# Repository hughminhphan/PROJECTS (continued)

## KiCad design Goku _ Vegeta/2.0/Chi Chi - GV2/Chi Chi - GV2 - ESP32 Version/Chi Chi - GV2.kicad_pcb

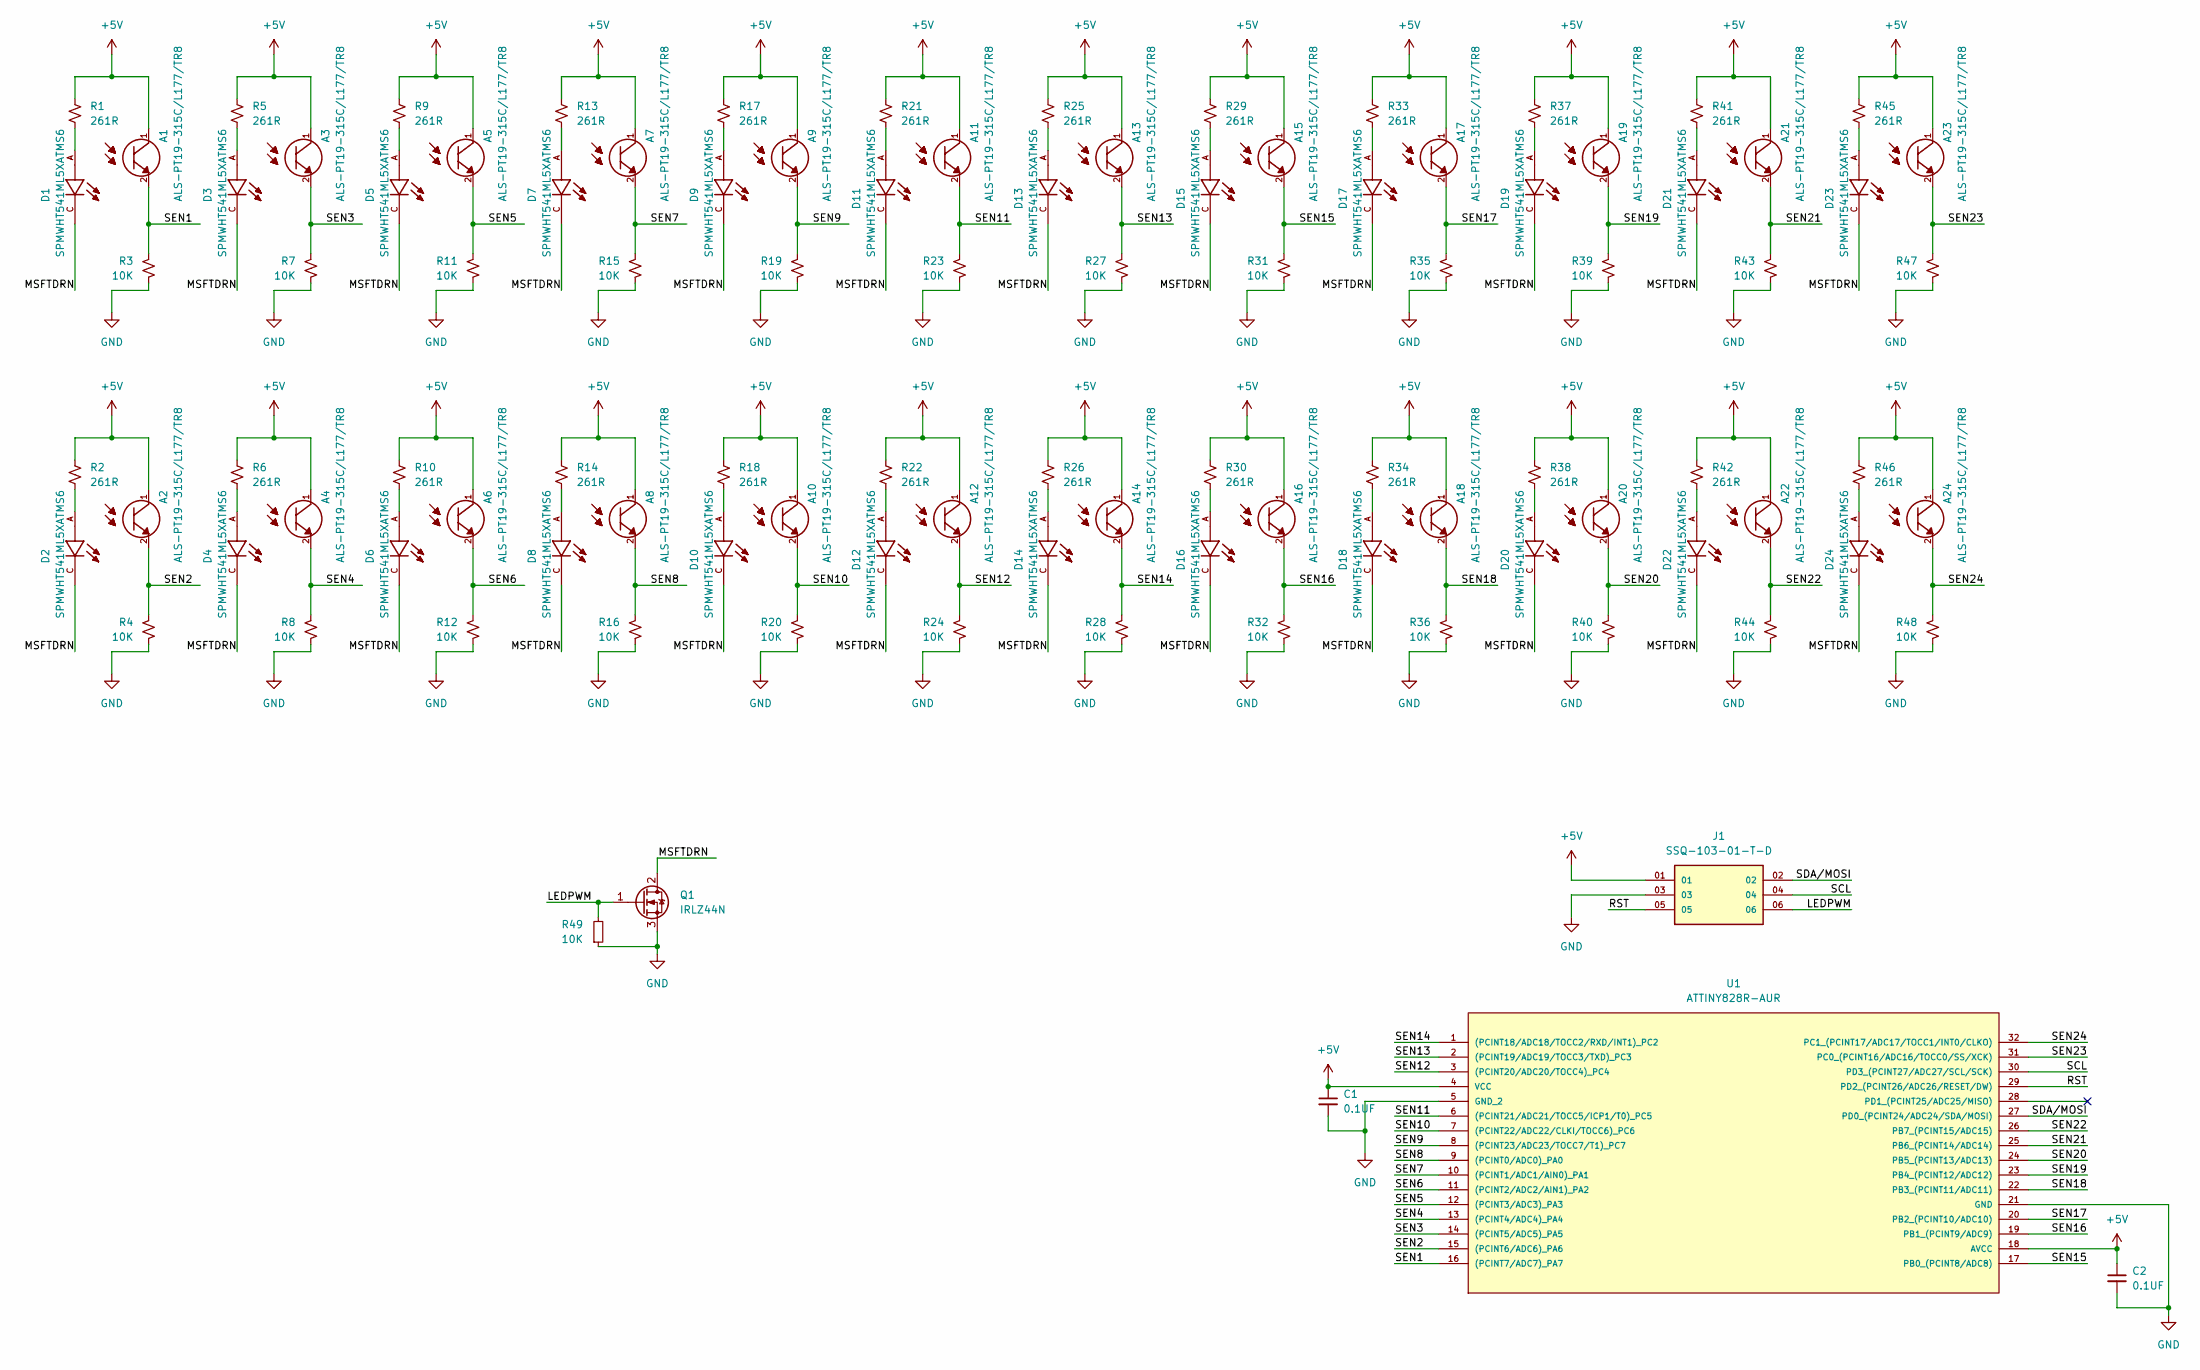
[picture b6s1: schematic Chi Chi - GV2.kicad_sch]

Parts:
A1, A2, A3, A4, A5, A6, A7, A8, A9, A10, A11, A12, A13, A14, A15, A16, A17, A18, A19, A20, A21, A22, A23, A24: ALS-PT19-315C/L177/TR8; XDCR_ALS-PT19-315C_L177_TR8; PARTREV 5
C1, C2: 0.1UF; C_0805_2012Metric_Pad1.18x1.45mm_HandSolder
D1, D2, D3, D4, D5, D6, D7, D8, D9, D10, D11, D12, D13, D14, D15, D16, D17, D18, D19, D20, D21, D22, D23, D24: SPMWHT541ML5XATMS6; LED_SPMWHT541MP5WAPKS4; PARTREV 8.3
J1: SSQ-103-01-T-D; SAMTEC_SSQ-103-01-T-D; PARTREV R
Q1: IRLZ44N; TO-220-3_Vertical
R1, R2, R5, R6, R9, R10, R13, R14, R17, R18, R21, R22, R25, R26, R29, R30, R33, R34, R37, R38, R41, R42, R45, R46: 261R; R_0805_2012Metric_Pad1.20x1.40mm_HandSolder
R3, R4, R7, R8, R11, R12, R15, R16, R19, R20, R23, R24, R27, R28, R31, R32, R35, R36, R39, R40, R43, R44, R47, R48: 10K; R_0805_2012Metric_Pad1.20x1.40mm_HandSolder
R49: 10K; R_0805_2012Metric
U1: ATTINY828R-AUR; TQFP32_9X9_MCH; MANUFACTURER_PART_NUMBER ATTINY828R-AUR

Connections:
+5V: A1.1, A2.1, A3.1, A4.1, A5.1, A6.1, A7.1, A8.1, A9.1, A10.1, A11.1, A12.1, A13.1, A14.1, A15.1, A16.1, A17.1, A18.1, A19.1, A20.1, A21.1, A22.1, A23.1, A24.1, C1.1, C2.1, J1.01, R1.1, R2.1, R5.1, R6.1, R9.1, R10.1, R13.1, R14.1, R17.1, R18.1, R21.1, R22.1, R25.1, R26.1, R29.1, R30.1, R33.1, R34.1, R37.1, R38.1, R41.1, R42.1, R45.1, R46.1, U1.4 (VCC), U1.18 (AVCC)
/LEDPWM: J1.06, Q1.1 (G), R49.2
/MSFTDRN: D1.C, D2.C, D3.C, D4.C, D5.C, D6.C, D7.C, D8.C, D9.C, D10.C, D11.C, D12.C, D13.C, D14.C, D15.C, D16.C, D17.C, D18.C, D19.C, D20.C, D21.C, D22.C, D23.C, D24.C, Q1.2 (D)
/RST: J1.05, U1.29 (PD2_(PCINT26/ADC26/RESET/DW))
/SCL: J1.04, U1.30 (PD3_(PCINT27/ADC27/SCL/SCK))
/SDA/MOSI: J1.02, U1.27 (PD0_(PCINT24/ADC24/SDA/MOSI))
/SEN1: A1.2, R3.2, U1.16 ((PCINT7/ADC7)_PA7)
/SEN2: A2.2, R4.2, U1.15 ((PCINT6/ADC6)_PA6)
/SEN3: A3.2, R7.2, U1.14 ((PCINT5/ADC5)_PA5)
/SEN4: A4.2, R8.2, U1.13 ((PCINT4/ADC4)_PA4)
/SEN5: A5.2, R11.2, U1.12 ((PCINT3/ADC3)_PA3)
/SEN6: A6.2, R12.2, U1.11 ((PCINT2/ADC2/AIN1)_PA2)
/SEN7: A7.2, R15.2, U1.10 ((PCINT1/ADC1/AIN0)_PA1)
/SEN8: A8.2, R16.2, U1.9 ((PCINT0/ADC0)_PA0)
/SEN9: A9.2, R19.2, U1.8 ((PCINT23/ADC23/TOCC7/T1)_PC7)
/SEN10: A10.2, R20.2, U1.7 ((PCINT22/ADC22/CLKI/TOCC6)_PC6)
/SEN11: A11.2, R23.2, U1.6 ((PCINT21/ADC21/TOCC5/ICP1/T0)_PC5)
/SEN12: A12.2, R24.2, U1.3 ((PCINT20/ADC20/TOCC4)_PC4)
/SEN13: A13.2, R27.2, U1.2 ((PCINT19/ADC19/TOCC3/TXD)_PC3)
/SEN14: A14.2, R28.2, U1.1 ((PCINT18/ADC18/TOCC2/RXD/INT1)_PC2)
/SEN15: A15.2, R31.2, U1.17 (PB0_(PCINT8/ADC8))
/SEN16: A16.2, R32.2, U1.19 (PB1_(PCINT9/ADC9))
/SEN17: A17.2, R35.2, U1.20 (PB2_(PCINT10/ADC10))
/SEN18: A18.2, R36.2, U1.22 (PB3_(PCINT11/ADC11))
/SEN19: A19.2, R39.2, U1.23 (PB4_(PCINT12/ADC12))
/SEN20: A20.2, R40.2, U1.24 (PB5_(PCINT13/ADC13))
/SEN21: A21.2, R43.2, U1.25 (PB6_(PCINT14/ADC14))
/SEN22: A22.2, R44.2, U1.26 (PB7_(PCINT15/ADC15))
/SEN23: A23.2, R47.2, U1.31 (PC0_(PCINT16/ADC16/TOCC0/SS/XCK))
/SEN24: A24.2, R48.2, U1.32 (PC1_(PCINT17/ADC17/TOCC1/INT0/CLKO))
GND: C1.2, C2.2, J1.03, Q1.3 (S), R3.1, R4.1, R7.1, R8.1, R11.1, R12.1, R15.1, R16.1, R19.1, R20.1, R23.1, R24.1, R27.1, R28.1, R31.1, R32.1, R35.1, R36.1, R39.1, R40.1, R43.1, R44.1, R47.1, R48.1, R49.1, U1.5 (GND_2), U1.21 (GND)
unnamed: D1.A, R1.2
unnamed: D2.A, R2.2
unnamed: D3.A, R5.2
unnamed: D4.A, R6.2
unnamed: D5.A, R9.2
unnamed: D6.A, R10.2
unnamed: D7.A, R13.2
unnamed: D8.A, R14.2
unnamed: D9.A, R17.2
unnamed: D10.A, R18.2
unnamed: D11.A, R21.2
unnamed: D12.A, R22.2
unnamed: D13.A, R25.2
unnamed: D14.A, R26.2
unnamed: D15.A, R29.2
unnamed: D16.A, R30.2
unnamed: D17.A, R33.2
unnamed: D18.A, R34.2
unnamed: D19.A, R37.2
unnamed: D20.A, R38.2
unnamed: D21.A, R41.2
unnamed: D22.A, R42.2
unnamed: D23.A, R45.2
unnamed: D24.A, R46.2

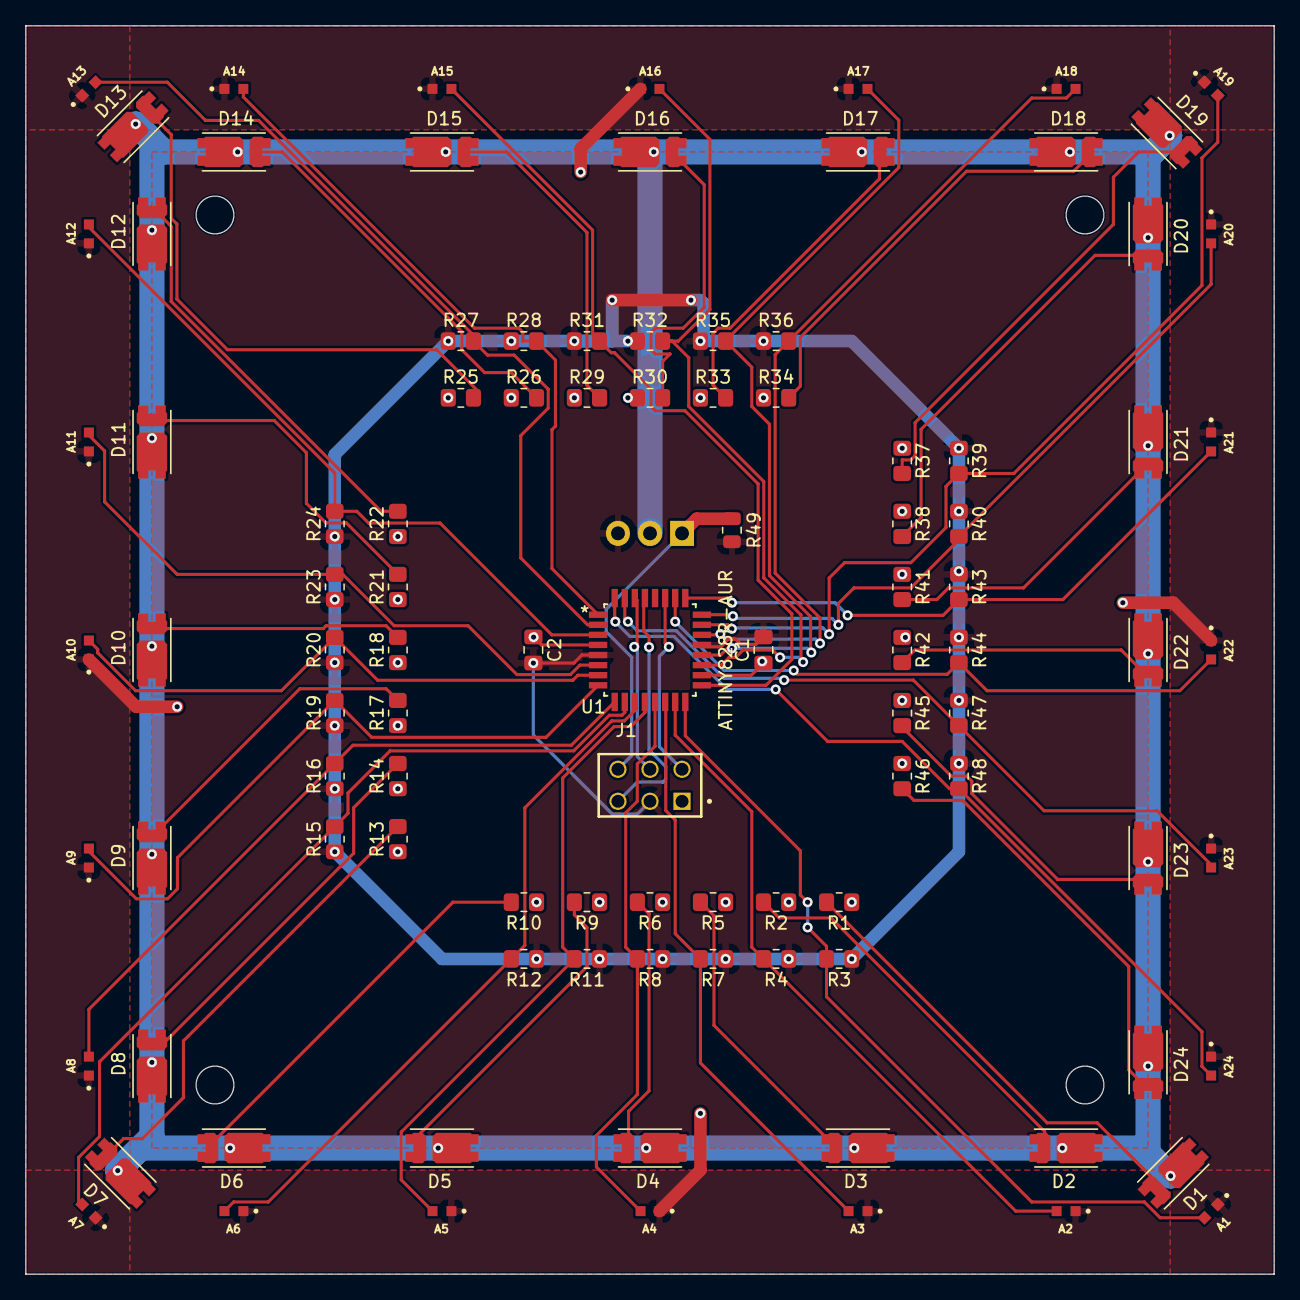
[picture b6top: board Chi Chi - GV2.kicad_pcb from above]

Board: 2 copper layers, 99.0 x 99.0 mm, 102 parts (1 on the bottom side), 55 nets.

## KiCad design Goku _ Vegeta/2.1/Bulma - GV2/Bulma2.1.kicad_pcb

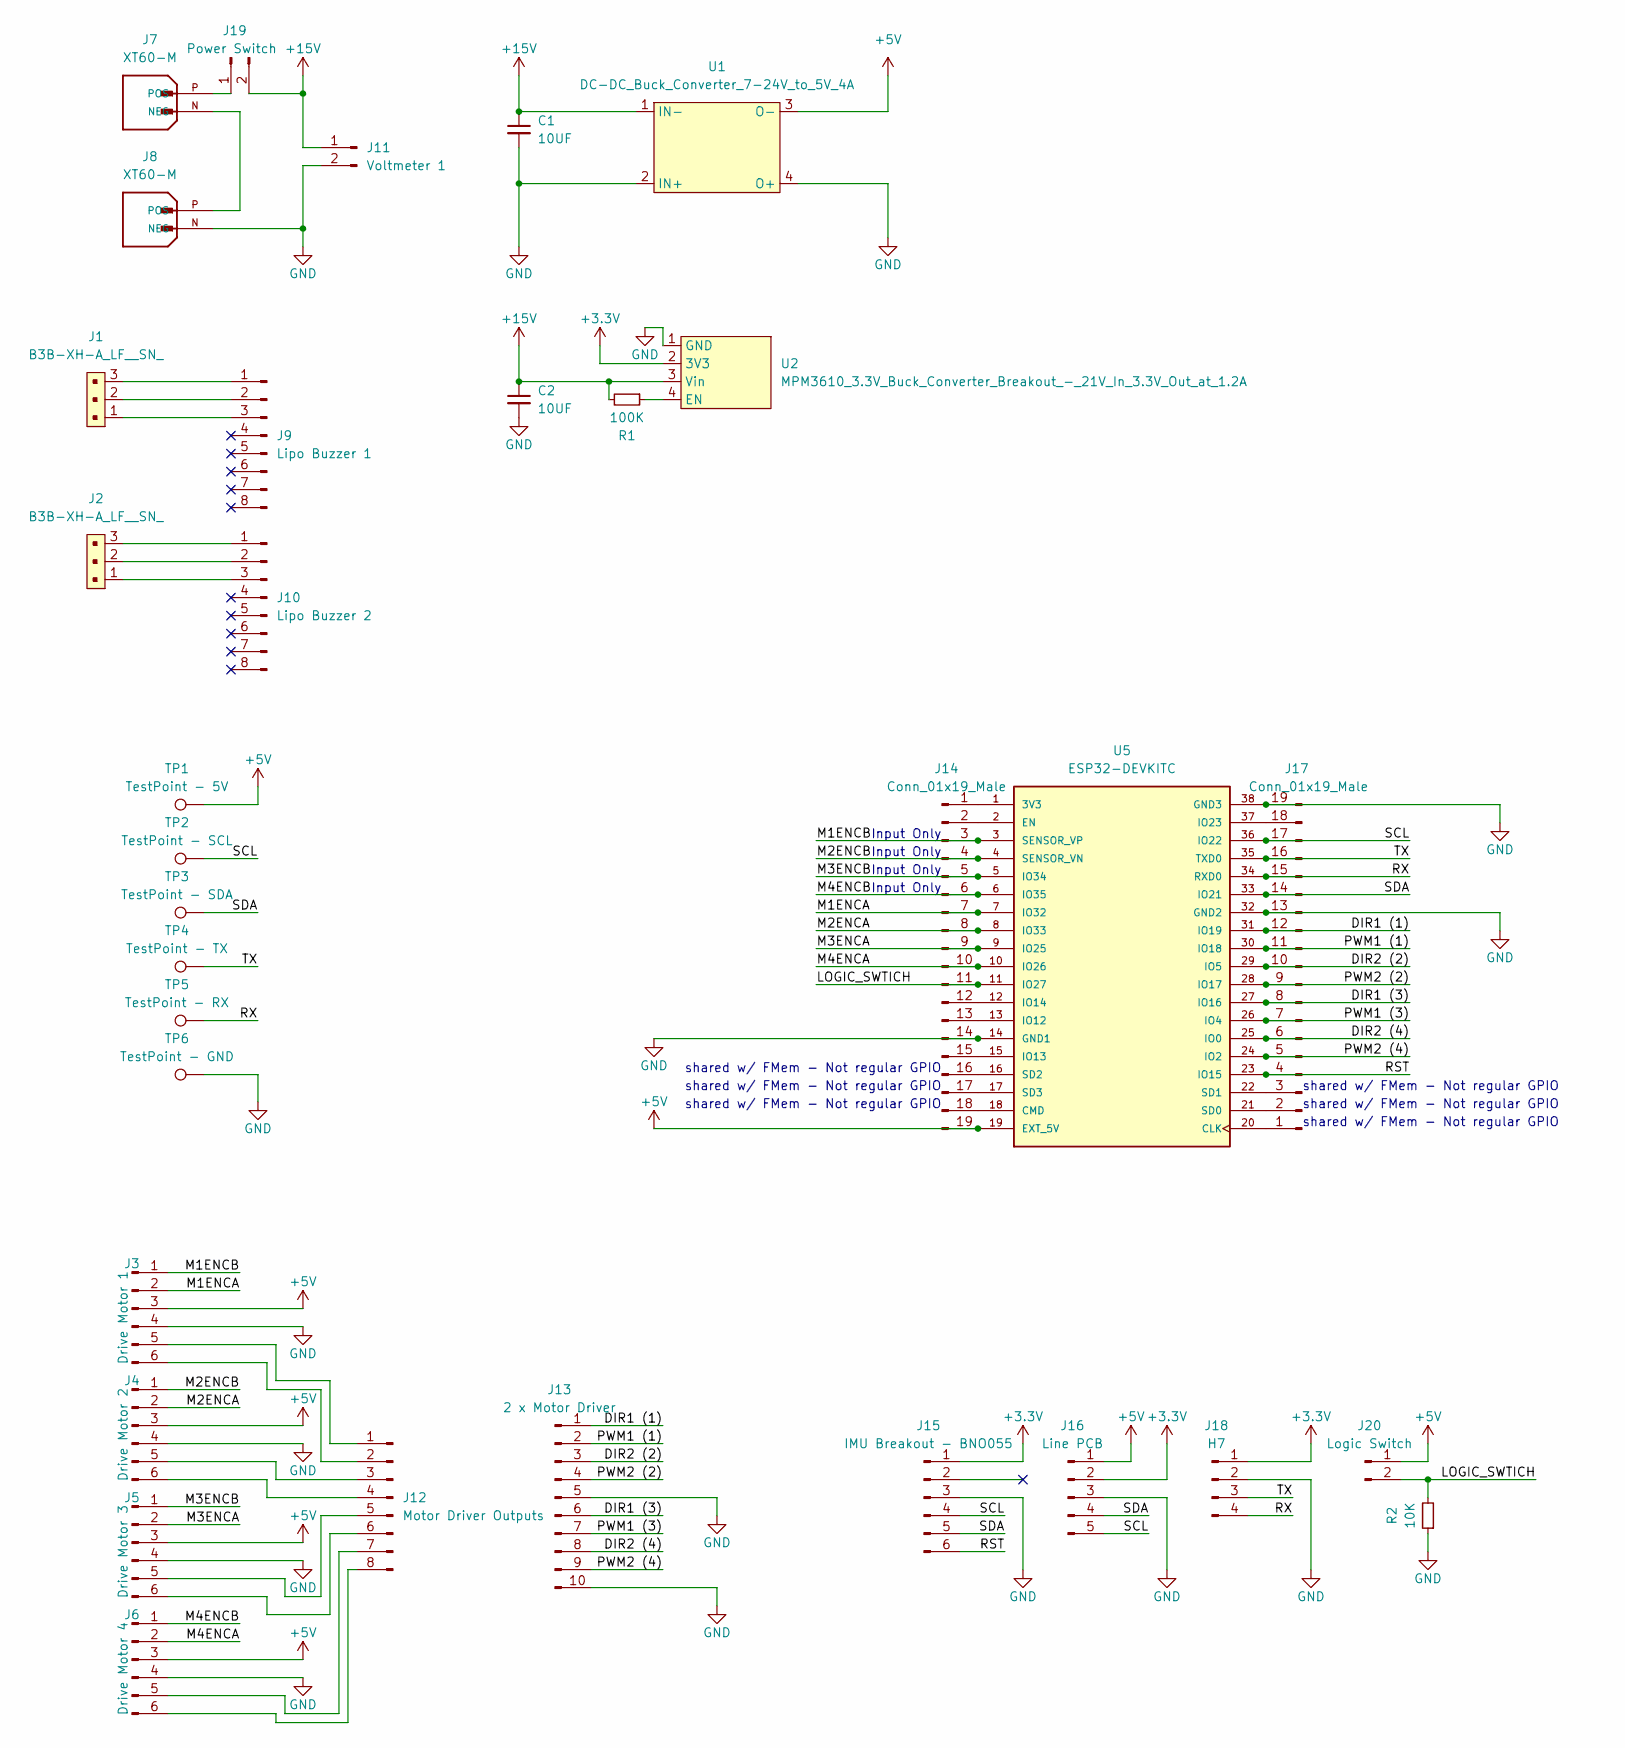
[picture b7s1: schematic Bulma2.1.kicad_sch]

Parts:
C1, C2: 10UF; C_0805_2012Metric
J1, J2: B3B-XH-A_LF__SN_; PinHeader_1x3_P2.5mm_Drill1.1mm; MPN B3B-XH-A(LF)(SN); Digi-Key_PN 455-2248-ND
J3: Drive Motor 1; PinSocket_1x06_P2.54mm_Vertical
J4: Drive Motor 2; PinHeader_1x06_P2.54mm_Vertical
J5: Drive Motor 3; PinSocket_1x06_P2.54mm_Vertical
J6: Drive Motor 4; PinSocket_1x06_P2.54mm_Vertical
J7, J8: XT60-M; AMASS_XT60-M; PARTREV V1.2
J9: Lipo Buzzer 1; Lipo Buzzer Vertical
J10: Lipo Buzzer 2; Lipo Buzzer Vertical
J11: Voltmeter 1; PinHeader_1x02_P2.54mm_Vertical
J12: Motor Driver Outputs; PinHeader_1x08_P2.54mm_Vertical
J13: 2 x Motor Driver; PinHeader_1x10_P2.54mm_Vertical
J14, J17: Conn_01x19_Male; PinHeader_1x19_P2.54mm_Vertical
J15: IMU Breakout - BNO055; Adafruit IMU BNO055
J16: Line PCB; PinHeader_1x05_P2.54mm_Vertical
J18: H7; PinHeader_1x04_P2.54mm_Vertical
J19: Power Switch; PinHeader_1x02_P2.54mm_Vertical
J20: Logic Switch; PinHeader_1x02_P2.54mm_Vertical
R1: 100K; R_0805_2012Metric
R2: 10K; R_0805_2012Metric
TP1: TestPoint - 5V; TestPoint_THTPad_D2.0mm_Drill1.0mm
TP2: TestPoint - SCL; TestPoint_THTPad_D2.0mm_Drill1.0mm
TP3: TestPoint - SDA; TestPoint_THTPad_D2.0mm_Drill1.0mm
TP4: TestPoint - TX; TestPoint_THTPad_D2.0mm_Drill1.0mm
TP5: TestPoint - RX; TestPoint_THTPad_D2.0mm_Drill1.0mm
TP6: TestPoint - GND; TestPoint_THTPad_D2.0mm_Drill1.0mm
U1: DC-DC_Buck_Converter_7-24V_to_5V_4A
U2: MPM3610_3.3V_Buck_Converter_Breakout_-_21V_In_3.3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; MPM3610 3.3V Buck Converter Breakout - 21V In 3.3V Out at 1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
U5: ESP32-DEVKITC; MODULE_ESP32-DEVKITC; PARTREV N/A

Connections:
+3.3V: J15.1, J16.2, J18.1, U2.2 (3V3)
+5V: J3.3, J4.3, J5.3, J6.3, J14.19, J16.1, J20.1, TP1.1, U1.3 (O-), U5.19 (EXT_5V)
+15V: C1.1, C2.1, J11.1, J19.2, R1.2, U1.1 (IN-), U2.3 (Vin)
/DIR1 (1): J13.1, J17.12, U5.31 (IO19)
/DIR1 (3): J13.6, J17.8, U5.27 (IO16)
/DIR2 (2): J13.3, J17.10, U5.29 (IO5)
/DIR2 (4): J13.8, J17.6, U5.25 (IO0)
/LOGIC_SWTICH: J14.11, J20.2, R2.2, U5.11 (IO27)
/M1ENCA: J3.2, J14.7, U5.7 (IO32)
/M1ENCB: J3.1, J14.3, U5.3 (SENSOR_VP)
/M2ENCA: J4.2, J14.8, U5.8 (IO33)
/M2ENCB: J4.1, J14.4, U5.4 (SENSOR_VN)
/M3ENCA: J5.2, J14.9, U5.9 (IO25)
/M3ENCB: J5.1, J14.5, U5.5 (IO34)
/M4ENCA: J6.2, J14.10, U5.10 (IO26)
/M4ENCB: J6.1, J14.6, U5.6 (IO35)
/PWM1 (1): J13.2, J17.11, U5.30 (IO18)
/PWM1 (3): J13.7, J17.7, U5.26 (IO4)
/PWM2 (2): J13.4, J17.9, U5.28 (IO17)
/PWM2 (4): J13.9, J17.5, U5.24 (IO2)
/RST: J15.6, J17.4, U5.23 (IO15)
/RX: J17.15, J18.4, TP5.1, U5.34 (RXD0)
/SCL: J15.4, J16.5, J17.17, TP2.1, U5.36 (IO22)
/SDA: J15.5, J16.4, J17.14, TP3.1, U5.33 (IO21)
/TX: J17.16, J18.3, TP4.1, U5.35 (TXD0)
GND: C1.2, C2.2, J3.4, J4.4, J5.4, J6.4, J8.N (NEG), J11.2, J13.5, J13.10, J14.14, J15.3, J16.3, J17.13, J17.19, J18.2, R2.1, TP6.1, U1.2 (IN+), U1.4 (O+), U2.1 (GND), U5.14 (GND1), U5.32 (GND2), U5.38 (GND3)
unnamed: J7.N (NEG), J8.P (POS)
unnamed: J1.3, J9.1
unnamed: J1.2, J9.2
unnamed: J1.1, J9.3
unnamed: J2.3, J10.1
unnamed: J2.2, J10.2
unnamed: J2.1, J10.3
unnamed: J3.5, J12.1
unnamed: J3.6, J12.2
unnamed: J4.5, J12.3
unnamed: J4.6, J12.4
unnamed: J5.5, J12.5
unnamed: J5.6, J12.6
unnamed: J6.5, J12.7
unnamed: J6.6, J12.8
unnamed: J14.1, U5.1 (3V3)
unnamed: J14.2, U5.2 (EN)
unnamed: J14.12, U5.12 (IO14)
unnamed: J14.13, U5.13 (IO12)
unnamed: J14.15, U5.15 (IO13)
unnamed: J14.16, U5.16 (SD2)
unnamed: J14.17, U5.17 (SD3)
unnamed: J14.18, U5.18 (CMD)
unnamed: J17.1, U5.20 (CLK)
unnamed: J17.2, U5.21 (SD0)
unnamed: J17.3, U5.22 (SD1)
unnamed: J17.18, U5.37 (IO23)
unnamed: J7.P (POS), J19.1
unnamed: R1.1, U2.4 (EN)

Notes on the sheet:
Input Only
shared w/ FMem - Not regular GPIO

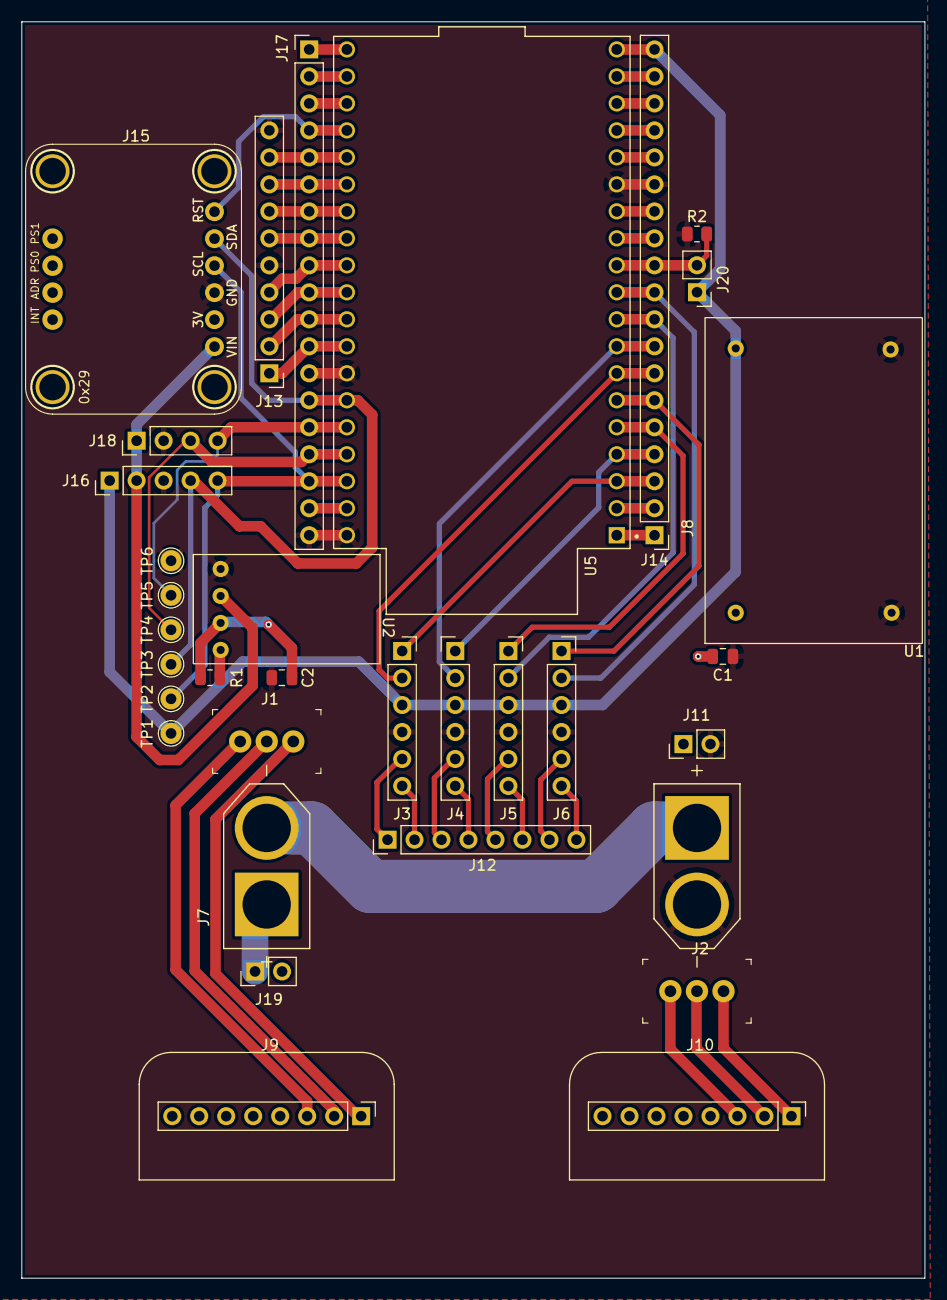
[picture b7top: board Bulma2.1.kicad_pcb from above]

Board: 2 copper layers, 85.0 x 118.2 mm, 33 parts (0 on the bottom side), 55 nets.

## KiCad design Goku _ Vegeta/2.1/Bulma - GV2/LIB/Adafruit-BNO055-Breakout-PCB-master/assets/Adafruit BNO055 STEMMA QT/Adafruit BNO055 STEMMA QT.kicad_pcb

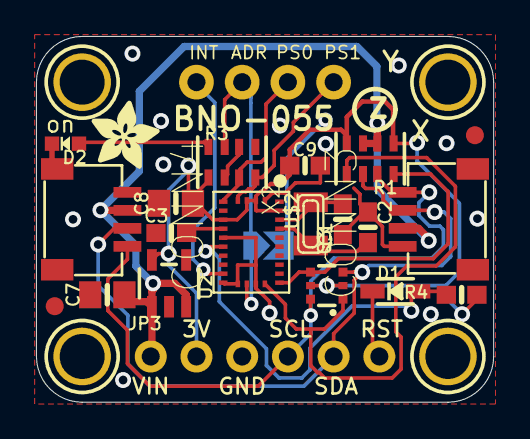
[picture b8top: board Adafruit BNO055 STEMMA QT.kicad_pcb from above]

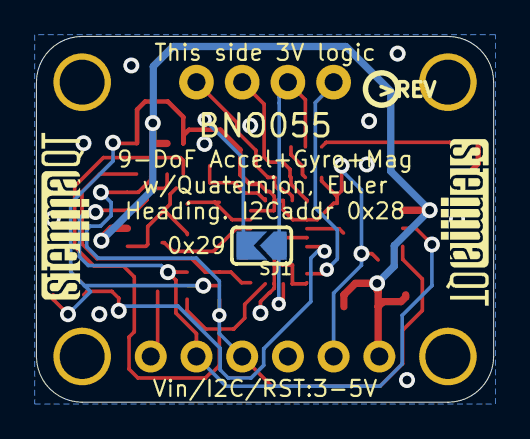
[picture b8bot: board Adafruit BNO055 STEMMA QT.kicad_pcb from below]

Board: 2 copper layers, 25.4 x 20.3 mm, 30 parts (4 on the bottom side), 17 nets.

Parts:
C1, C2: 22pF; 0603-NO
C3, C9: 0.1uF; 0603-NO
C7, C8: 10uF; 0805-NO
CONN3, CONN4: STEMMA_I2C_QT; JST_SH4
D1: 1n4148; SOD-323
D2: GREEN; CHIPLED_0603_NOOUTLINE
FID3, FID4: FIDUCIAL_1MM
JP2: 1X04_ROUND_76
JP3: 1X06_ROUND_70
Q3: BSS138; SOT363
R1, R3: 10K; RESPACK_4X0603
R4: 10K; 0603-NO
SJ1: SOLDERJUMPER_ARROW_NOPASTE
U2: AP2112K-3.3; SOT23-5
U$2: BNO055
U$45, U$46, U$48, U$49: MOUNTINGHOLE2.5; MOUNTINGHOLE_2.5_PLATED
U$51: ADAFRUIT_3.5MM
U$52: PCBFEAT-REV-040
U$53, U$54: STEMMAQT
X2: 32.768; XTAL3215

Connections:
3.3V: C8.1, C9.1, JP3.2, Q3.2, Q3.5, R1.1, R1.4, R3.1, R4.1, SJ1.2, U2.5, U$2.3, U$2.4, U$2.8, U$2.28
GND: C1.1, C2.1, C3.1, C7.2, C8.2, C9.2, CONN3.1, CONN3.MT1, CONN3.MT2, CONN4.1, CONN4.MT1, CONN4.MT2, D2.C, JP3.3, R3.2, R3.5, R3.6, U2.2, U$2.2, U$2.10, U$2.15, U$2.16, U$2.18, U$2.25
I2CADDR_3V: JP2.2, R3.7, SJ1.1, U$2.17
INT_3V: JP2.1, U$2.14
unnamed: C1.2, U$2.27, X2.P$2
unnamed: C2.2, U$2.26, X2.P$1
unnamed: C3.2, U$2.9
unnamed: D2.A, R3.8
NRESET_3V: D1.A, R4.2, U$2.11
PS0_3V: JP2.3, R3.3, U$2.6
PS1_3V: JP2.4, R3.4, U$2.5
RESET: D1.C, JP3.6
SCL: CONN3.4, CONN4.4, JP3.4, Q3.6, R1.7
SCL_3V: Q3.1, R1.5, U$2.19
SDA: CONN3.3, CONN4.3, JP3.5, Q3.3, R1.6
SDA_3V: Q3.4, R1.8, U$2.20
VCC: C7.1, CONN3.2, CONN4.2, JP3.1, R1.2, R1.3, U2.1, U2.3
